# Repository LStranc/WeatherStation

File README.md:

# WeatherStation
The goal of this project was to build a cordless personal weather station that can be put in your own backyard. The weather station sends data to a server and you can analyze, store and use the data in anyway you want. 

This project includes c file to upload to the microcontroller, the server files used to store data in the sql database and display it to the website, and the schematic and pcb files for the actual hardware.

## Hardware
The Mircocontoller I used in this project is the esp32. A more generalized arudino code file is uploaded to this repo also. The weather station reads temperature, humidity, and pressure through a BME280 chip. It has a water sensor to sense if it is rainig. It uses the solar panel to tell how bright/sunny it is outside. This solar panel is also charging the lipo battery that it is powering the weather station. There is a uv sensor that tells us the uv index. There is Wind Sensor Rev P made by Modern Devices that is able to measure the windspeed. Also, there is a PWM5005 sensor which measures the air quality. The esp samples each sensor input then sends the data wirelessly to the server.

## Server
The server stores the data from the weather station and puts it in a mySQL database. The server also hosts a website where a client can interact with current and previously stored data. 

## Future 
This project is still in progress but the hope for the future is to implement an machine algorithm to try to forcast the upcoming weather.

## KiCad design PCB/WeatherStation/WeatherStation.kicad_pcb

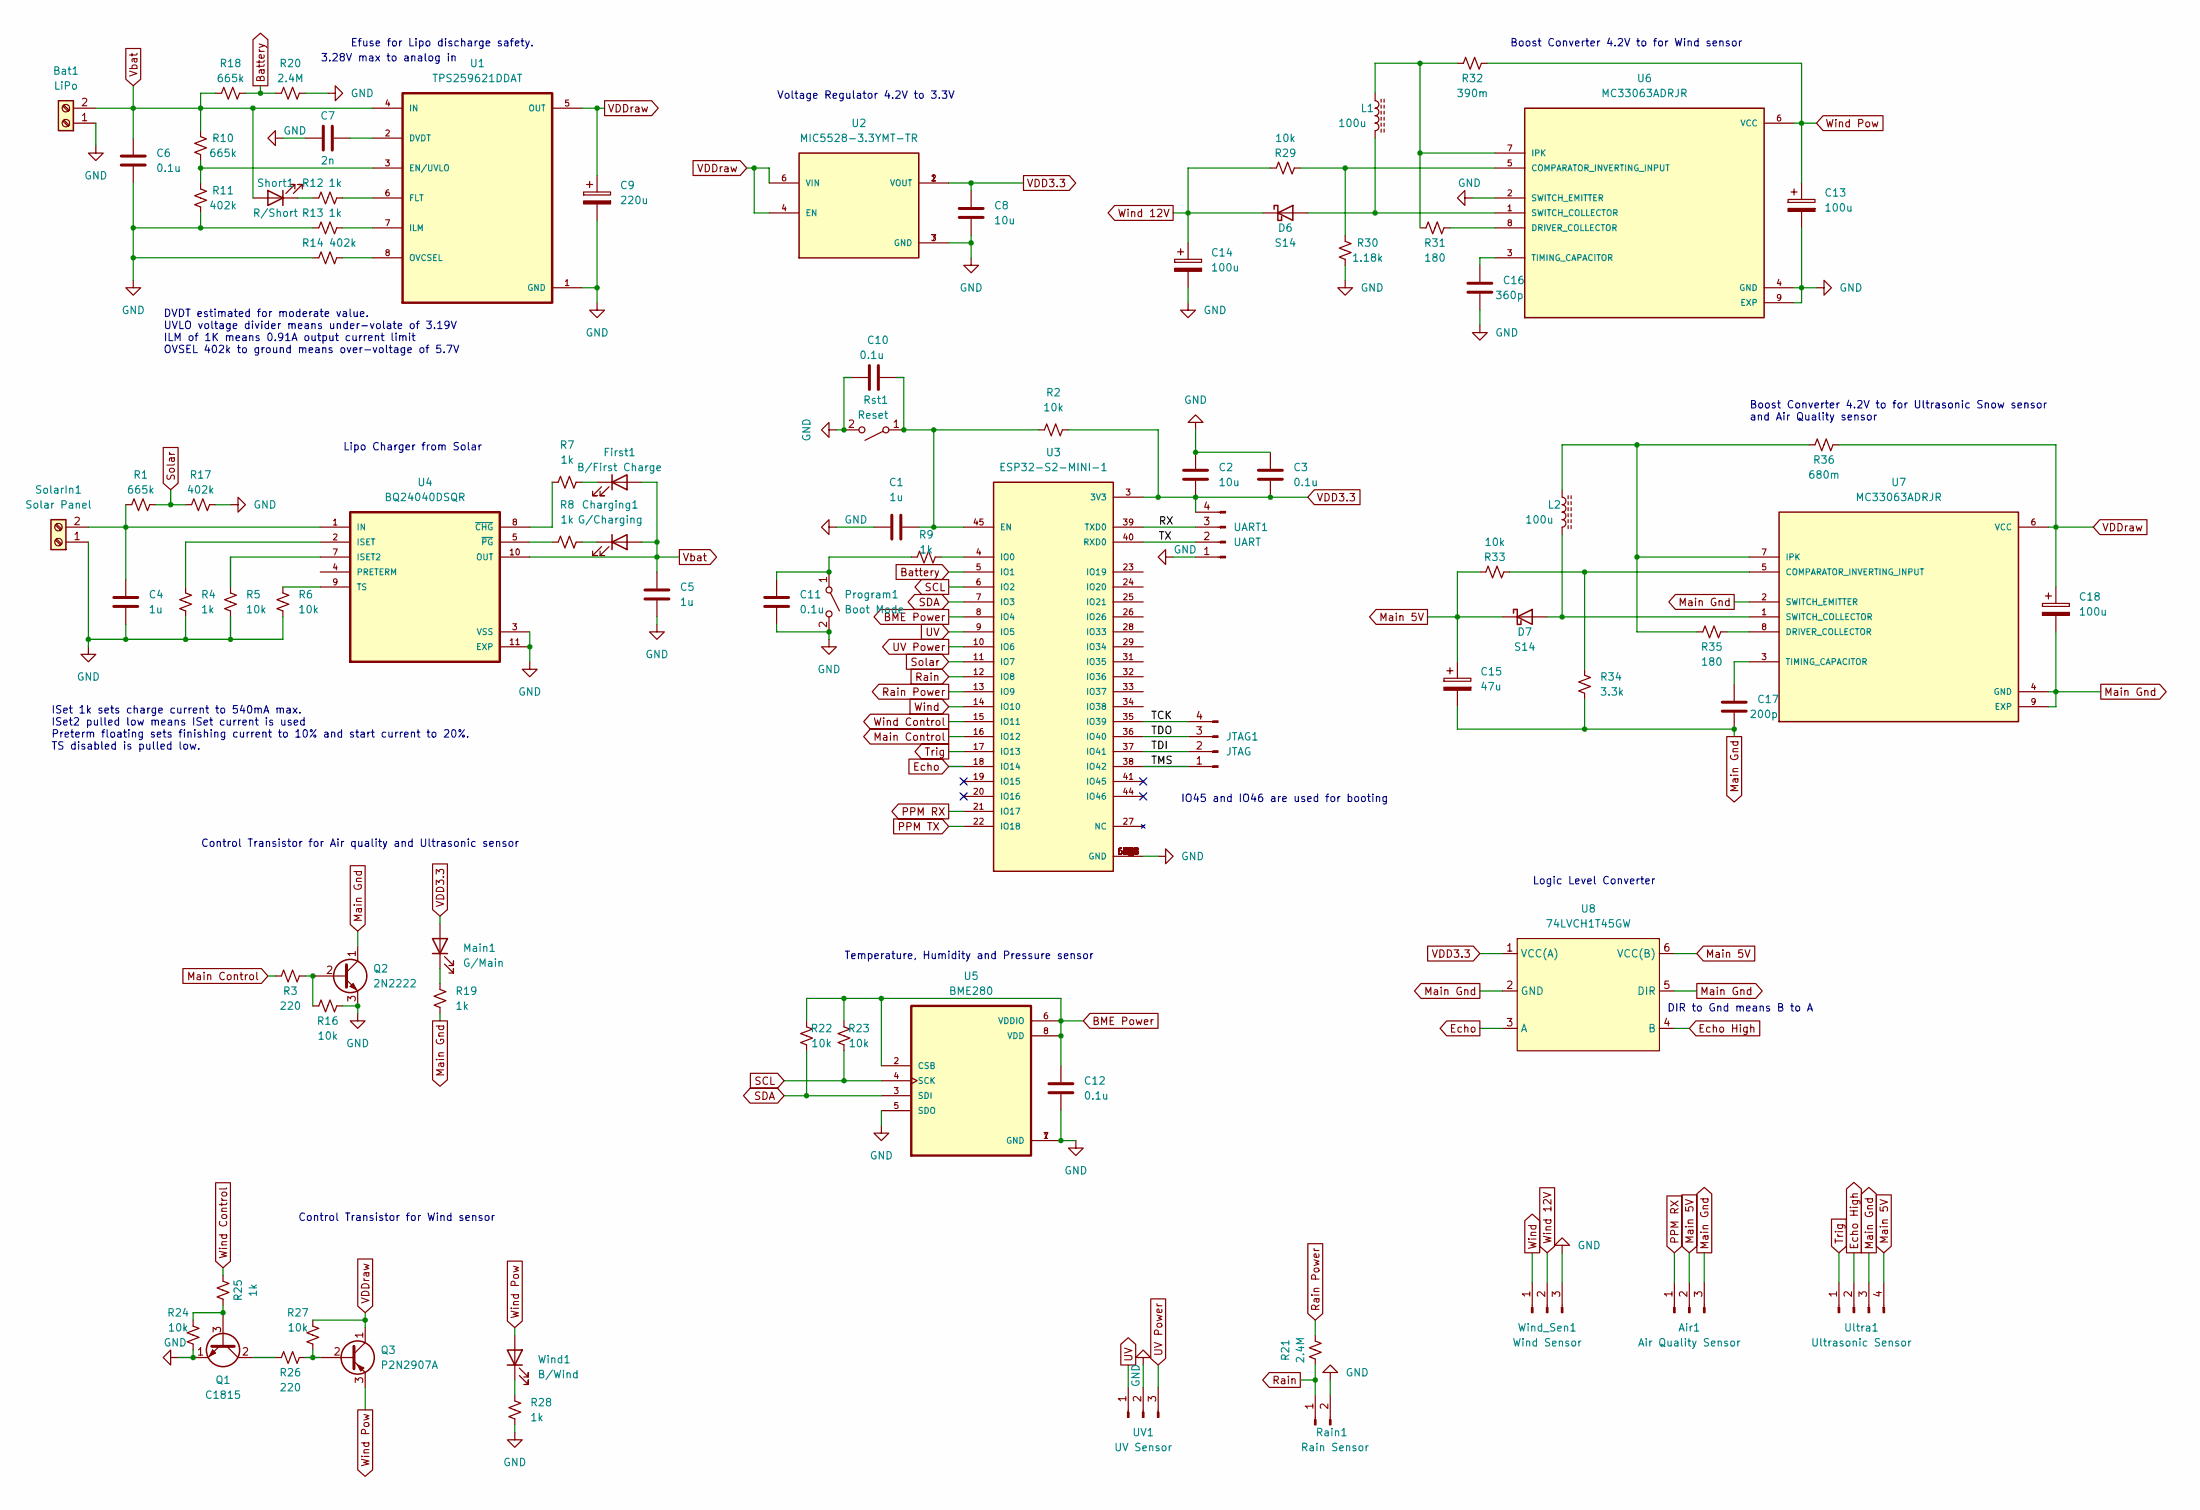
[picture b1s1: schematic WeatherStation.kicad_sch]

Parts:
Air1: Air Quality Sensor; PinHeader_1x03_P2.54mm_Vertical
Bat1: LiPo; TerminalBlock_Altech_AK300-2_P5.00mm
C1, C4, C5: 1u; C_0603_1608Metric_Pad1.08x0.95mm_HandSolder
C2, C8: 10u; C_0805_2012Metric_Pad1.18x1.45mm_HandSolder
C3, C6, C10, C11, C12: 0.1u; C_0603_1608Metric_Pad1.08x0.95mm_HandSolder
C7: 2n; C_0603_1608Metric_Pad1.08x0.95mm_HandSolder
C9: 220u; C_Radial_D5.0mm_H11.0mm_P2.00mm
C13, C18: 100u; C_Radial_D5.0mm_H11.0mm_P2.00mm
C14: 100u; C_Radial_D6.3mm_H11.0mm_P2.50mm
C15: 47u; C_Radial_D4.0mm_H7.0mm_P1.50mm
C16: 360p; C_0402_1005Metric_Pad0.74x0.62mm_HandSolder
C17: 200p; C_0603_1608Metric_Pad1.08x0.95mm_HandSolder
Charging1: G/Charging; LED_0603_1608Metric_Pad1.05x0.95mm_HandSolder
D6, D7: S14; D_SOD-123F
First1: B/First Charge; LED_0603_1608Metric_Pad1.05x0.95mm_HandSolder
JTAG1: JTAG; PinHeader_1x04_P2.54mm_Vertical
L1, L2: 100u; L_Toroid_Vertical_L10.2mm_W3.8mm_P3.8mm
Main1: G/Main; LED_0603_1608Metric_Pad1.05x0.95mm_HandSolder
Program1: Boot Mode; SW_PUSH_6mm_H5mm
Q1: C1815; TO-92
Q2: 2N2222; TO-92
Q3: P2N2907A; TO-92
R1, R10, R18: 665k; R_0603_1608Metric_Pad0.98x0.95mm_HandSolder
R2, R5, R6, R16, R22, R23, R24, R27, R29, R33: 10k; R_0603_1608Metric_Pad0.98x0.95mm_HandSolder
R3, R26: 220; R_0603_1608Metric_Pad0.98x0.95mm_HandSolder
R4, R7, R8, R9, R12, R13, R19, R25, R28: 1k; R_0603_1608Metric_Pad0.98x0.95mm_HandSolder
R11, R14, R17: 402k; R_0603_1608Metric_Pad0.98x0.95mm_HandSolder
R20, R21: 2.4M; R_0603_1608Metric_Pad0.98x0.95mm_HandSolder
R30: 1.18k; R_0603_1608Metric_Pad0.98x0.95mm_HandSolder
R31, R35: 180; R_0603_1608Metric_Pad0.98x0.95mm_HandSolder
R32: 390m; R_1206_3216Metric_Pad1.30x1.75mm_HandSolder
R34: 3.3k; R_0603_1608Metric_Pad0.98x0.95mm_HandSolder
R36: 680m; R_0603_1608Metric_Pad0.98x0.95mm_HandSolder
Rain1: Rain Sensor; PinHeader_1x02_P2.54mm_Vertical
Rst1: Reset; SW_PUSH_6mm_H5mm
Short1: R/Short; LED_0603_1608Metric_Pad1.05x0.95mm_HandSolder
SolarIn1: Solar Panel; TerminalBlock_Altech_AK300-2_P5.00mm
U1: TPS259621DDAT; VREG_LM5017MR_NOPB
U2: MIC5528-3.3YMT-TR; SON40P120X120X60-7N
U3: ESP32-S2-MINI-1; XCVR_ESP32-S2-MINI-1; PARTREV 1.0
U4: BQ24040DSQR; SON40P200X200X80-11N
U5: BME280; PSON65P250X250X100-8N
U6, U7: MC33063ADRJR; SON80P400X400X80-9N; PARTREV N
U8: 74LVCH1T45GW; SOT-363_SC-70-6_Handsoldering
UART1: UART; PinHeader_1x04_P2.54mm_Vertical
UV1: UV Sensor; PinHeader_1x03_P2.54mm_Vertical
Ultra1: Ultrasonic Sensor; PinHeader_1x04_P2.54mm_Vertical
Wind1: B/Wind; LED_0603_1608Metric_Pad1.05x0.95mm_HandSolder
Wind_Sen1: Wind Sensor; PinHeader_1x03_P2.54mm_Vertical

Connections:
/RX: U3.39 (TXD0), UART1.3
/TCK: JTAG1.4, U3.35 (IO39)
/TDI: JTAG1.2, U3.37 (IO41)
/TDO: JTAG1.3, U3.36 (IO40)
/TMS: JTAG1.1, U3.38 (IO42)
/TX: U3.40 (RXD0), UART1.2
BME Power: C12.1, R22.1, R23.1, U3.8 (IO4), U5.2 (CSB), U5.6 (VDDIO), U5.8 (VDD)
Battery: R18.2, R20.1, U3.5 (IO1)
Echo: U3.18 (IO14), U8.3 (A)
Echo High: U8.4 (B), Ultra1.2
GND: Bat1.1, C1.1, C2.1, C3.1, C4.1, C5.1, C6.2, C7.1, C8.2, C9.2, C10.2, C11.2, C12.2, C13.2, C14.2, C16.2, Program1.2 (B), Q1.1 (E), Q2.3 (E), R4.1, R5.1, R6.1, R11.2, R13.2, R14.2, R16.1, R17.2, R20.2, R24.2, R28.2, R30.1, Rain1.2, Rst1.2 (B), SolarIn1.1, U1.1 (GND), U2.3 (GND), U2.7 (GND), U3.1 (GND), U3.2 (GND), U3.30 (GND), U3.42 (GND), U3.43 (GND), U3.46 (GND), U3.47 (GND), U3.48 (GND), U3.49 (GND), U3.50 (GND), U3.51 (GND), U3.52 (GND), U3.53 (GND), U3.54 (GND), U3.55 (GND), U3.56 (GND), U3.57 (GND), U3.58 (GND), U3.59 (GND), U3.60 (GND), U3.61 (GND), U3.61_1 (GND), U3.61_2 (GND), U3.61_3 (GND), U3.61_4 (GND), U3.61_5 (GND), U3.61_6 (GND), U3.61_7 (GND), U3.61_8 (GND), U3.62 (GND), U3.63 (GND), U3.64 (GND), U3.65 (GND), U4.3 (VSS), U4.11 (EXP), U5.1 (GND), U5.5 (SDO), U5.7 (GND), U6.2 (SWITCH_EMITTER), U6.4 (GND), U6.9 (EXP), UART1.1, UV1.2, Wind_Sen1.3
Main 5V: Air1.2, C15.1, D7.1 (K), R33.2, U8.6 (VCC(B)), Ultra1.4
Main Control: R3.2, U3.16 (IO12)
Main Gnd: Air1.3, C15.2, C17.2, C18.2, Q2.1 (C), R19.2, R34.2, U7.2 (SWITCH_EMITTER), U7.4 (GND), U7.9 (EXP), U8.2 (GND), U8.5 (DIR), Ultra1.3
unnamed: C1.2, C10.1, R2.1, Rst1.1 (A), U3.45 (EN)
unnamed: C4.2, R1.1, SolarIn1.2, U4.1 (IN)
unnamed: C7.2, U1.2 (DVDT)
unnamed: C11.1, Program1.1 (A), R9.1
unnamed: C16.1, U6.3 (TIMING_CAPACITOR)
unnamed: C17.1, U7.3 (TIMING_CAPACITOR)
unnamed: Charging1.1 (K), R8.1
unnamed: D6.2 (A), L1.2, U6.1 (SWITCH_COLLECTOR)
unnamed: D7.2 (A), L2.2, U7.1 (SWITCH_COLLECTOR)
unnamed: First1.1 (K), R7.1
unnamed: L1.1, R31.1, R32.1, U6.7 (IPK)
unnamed: L2.1, R35.1, R36.1, U7.7 (IPK)
unnamed: Main1.1 (K), R19.1
unnamed: Q1.2 (C), R26.1
unnamed: Q1.3 (B), R24.1, R25.2
unnamed: Q2.2 (B), R3.1, R16.2
unnamed: Q3.2 (B), R26.2, R27.2
unnamed: R4.2, U4.2 (ISET)
unnamed: R5.2, U4.7 (ISET2)
unnamed: R6.2, U4.9 (TS)
unnamed: R7.2, U4.8 (~CHG)
unnamed: R8.2, U4.5 (~PG)
unnamed: R9.2, U3.4 (IO0)
unnamed: R10.2, R11.1, U1.3 (EN/UVLO)
unnamed: R12.1, U1.6 (FLT)
unnamed: R12.2, Short1.1 (K)
unnamed: R13.1, U1.7 (ILM)
unnamed: R14.1, U1.8 (OVCSEL)
unnamed: R28.1, Wind1.1 (K)
unnamed: R29.1, R30.2, U6.5 (COMPARATOR_INVERTING_INPUT)
unnamed: R31.2, U6.8 (DRIVER_COLLECTOR)
unnamed: R33.1, R34.1, U7.5 (COMPARATOR_INVERTING_INPUT)
unnamed: R35.2, U7.8 (DRIVER_COLLECTOR)
PPM RX: Air1.1, U3.21 (IO17)
PPM TX: U3.22 (IO18)
Rain: R21.1, Rain1.1, U3.12 (IO8)
Rain Power: R21.2, U3.13 (IO9)
SCL: R23.2, U3.6 (IO2), U5.4 (SCK)
SDA: R22.2, U3.7 (IO3), U5.3 (SDI)
Solar: R1.2, R17.1, U3.11 (IO7)
Trig: U3.17 (IO13), Ultra1.1
UV: U3.9 (IO5), UV1.1
UV Power: U3.10 (IO6), UV1.3
VDD3.3: C2.2, C3.2, C8.1, Main1.2 (A), R2.2, U2.1 (VOUT), U2.2 (VOUT), U3.3 (3V3), U8.1 (VCC(A)), UART1.4
VDDraw: C9.1, C18.1, Q3.1 (C), R27.1, R36.2, U1.5 (OUT), U2.4 (EN), U2.6 (VIN), U7.6 (VCC)
Vbat: Bat1.2, C5.2, C6.1, Charging1.2 (A), First1.2 (A), R10.1, R18.1, Short1.2 (A), U1.4 (IN), U4.10 (OUT)
Wind: U3.14 (IO10), Wind_Sen1.1
Wind 12V: C14.1, D6.1 (K), R29.2, Wind_Sen1.2
Wind Control: R25.1, U3.15 (IO11)
Wind Pow: C13.1, Q3.3 (E), R32.2, U6.6 (VCC), Wind1.2 (A)

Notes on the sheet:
Temperature, Humidity and Pressure sensor
3.28V max to analog in
DVDT estimated for moderate value. UVLO voltage divider means under-volate of 3.19V ILM of 1K means 0.91A output current limit OVSEL 402k to ground means over-voltage of 5.7V
IO45 and IO46 are used for booting
Logic Level Converter
DIR to Gnd means B to A
Lipo Charger from Solar
Boost Converter 4.2V to for Wind sensor
ISet 1k sets charge current to 540mA max. ISet2 pulled low means ISet current is used Preterm floating sets finishing current to 10% and start current to 20%. TS disabled is pulled low.
Control Transistor for Air quality and Ultrasonic sensor
Voltage Regulator 4.2V to 3.3V
Efuse for Lipo discharge safety.
Control Transistor for Wind sensor
Boost Converter 4.2V to for Ultrasonic Snow sensor and Air Quality sensor

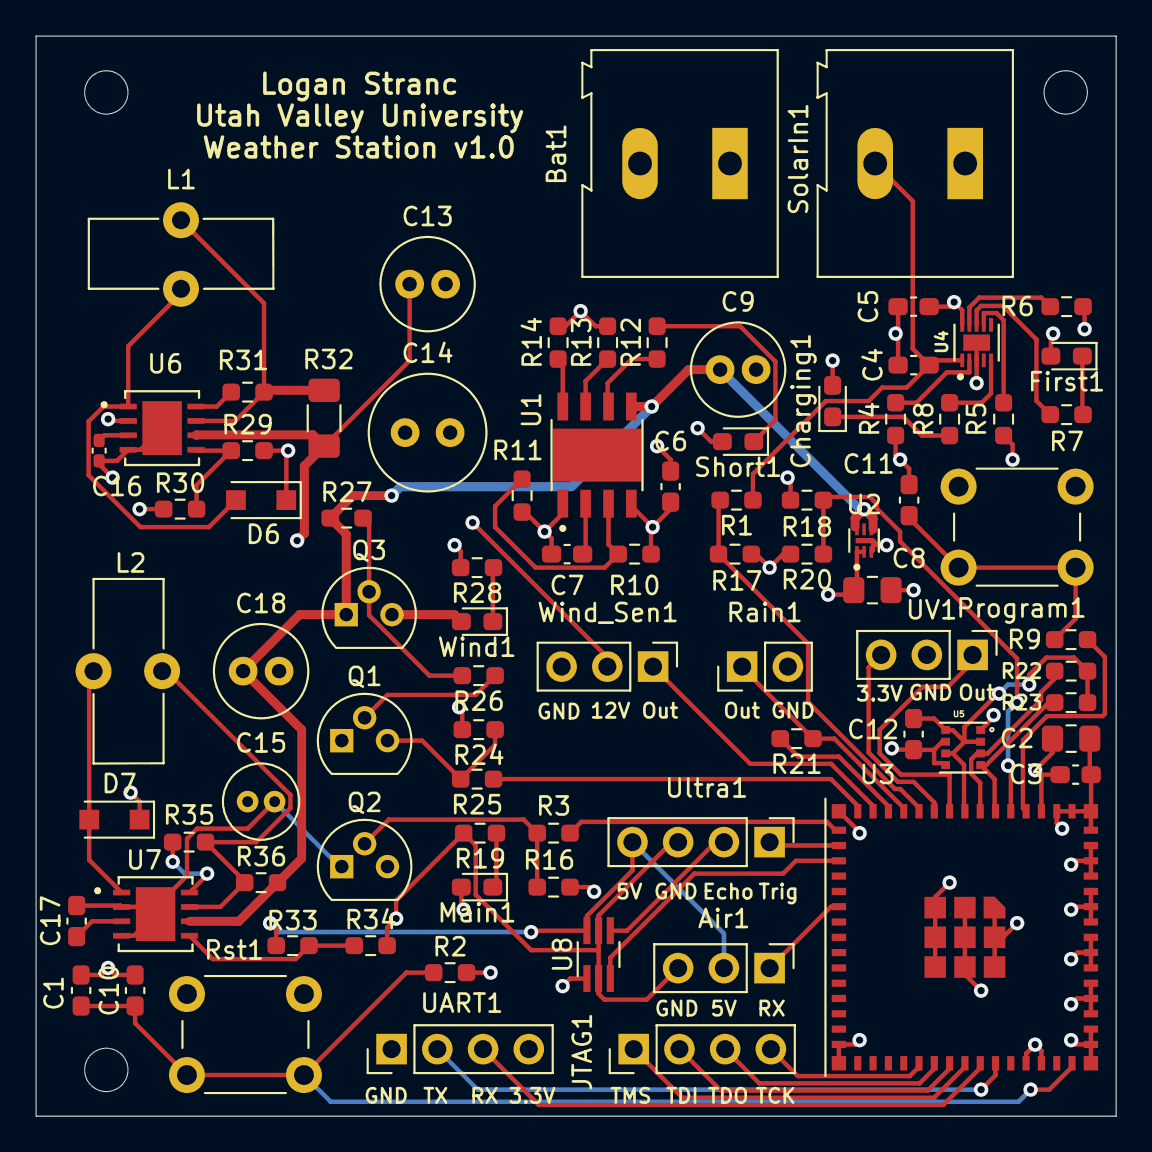
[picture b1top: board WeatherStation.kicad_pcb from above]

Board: 4 copper layers, 60.0 x 60.0 mm, 84 parts (0 on the bottom side), 63 nets.

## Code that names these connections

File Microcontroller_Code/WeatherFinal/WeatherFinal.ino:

#include "LowPower.h" //for sleep periods of microcontroller
#include <SoftwareSerial.h> // for serial communication needed for esp and air sensor
#include "Adafruit_PM25AQI.h" //air sensor library for easy interface
//BMP280 Packages
#include <Wire.h>
#include <Adafruit_Sensor.h>
#include <Adafruit_BME280.h>

#include "encrypt.h" //import ip and wifi connection information

// pins tx(pin 0) and rx(pin 1) are left floating
#define TRIGPIN 4 //ultrasonic trigger
#define ECHOPIN 5 //ultrasonic echo
#define POWERESP 8 //power for esp
#define POWERMAIN 9 //power for bme, rain, and uv sensors
#define POWERWIND 10 //power for wind sensor
#define BATTERYPIN A1 //battery voltage pin
#define SUNPIN A2 // solar panel voltage pin
#define WINDPIN A3 //wind sensor pin
#define UVPIN A6  // uv light sensor pin
#define RAINPIN A7 //Rain sensor pin

#define SERIALSPEED 115200               
#define DEBUG false 
SoftwareSerial esp8266(11,12);                   

SoftwareSerial pmSerial(2, 3); //only tx pin 2 is used, rx pin 3 is floating
Adafruit_PM25AQI aqi = Adafruit_PM25AQI();
PM25_AQI_Data data;

Adafruit_BME280 bme; // creates I2C BMP280 object, uses pins

float temperature = 0.0;
long pressure = 0;
float humidity = 0;
int precipitation = 0;
int sun = 800;
float windSpeed = 0;
int uvIndex = 1;
long cm = 0;
int battery = 0;

 
void setup(){
  Serial.begin(SERIALSPEED); 
  intPins();
}

void loop(){
  //sun = analogRead(SUNPIN); //store sun voltage reading
  deepSleep(30);
  battery = analogRead(BATTERYPIN); //store battery voltage reading
  delay(5000);
  readMainBus(); //reads data from bme, rain, and uv sensor
  delay(5000); // heavy load to heavy load, let circuit reach steady state 
  readWindBus(); // reads data from wind sensor
  delay(5000);
  sendWiFiOnBus(); //powerup and initialize esp and send weather data
  deepSleep(5); // sleep for 5*8= 40seconds
}

void deepSleep(int EightSecondIntervals){
  int i = 0;
  while(i<EightSecondIntervals){
  LowPower.powerDown(SLEEP_8S, ADC_OFF, BOD_OFF); //deep sleep for 8 seconds
  i++;
  } 
}

void intPins(){
  pinMode(POWERMAIN,OUTPUT);
  pinMode(POWERWIND,OUTPUT);
  pinMode(POWERESP,OUTPUT);
  digitalWrite(POWERMAIN, LOW);
  digitalWrite(POWERWIND, LOW);
  digitalWrite(POWERESP, LOW);

  
  //Ultrasonic sensor setup pins
  pinMode(TRIGPIN, INPUT); //InputPullup = 28uA, Input = 0 uA
  pinMode(ECHOPIN, INPUT); //InputPullup = 33 uA, Input
}

void readMainBus(){
  digitalWrite(POWERMAIN,HIGH); //give main bus power
  pinMode(TRIGPIN,OUTPUT);
  pinMode(ECHOPIN, INPUT); // set echo pin back to input
  delay(500);
  bme.begin(0x76); // bme initialize
  delay(2000); 
  temperature = bme.readTemperature(); //store temperature
  pressure = bme.readPressure(); //store pressure
  humidity = bme.readHumidity(); //store humidity
  delay(500);
  uvIndex = analogRead(UVPIN); //store uv voltage reading
  precipitation = analogRead(RAINPIN); //store precipitation voltage reading
  delay(1000);
  snowSensorRead(); // read snow height data
  delay(15000); //let sensor warmup for 15 seconds  
  airSensorRead(); // read air quality data 
  pinMode(TRIGPIN, INPUT); //set trigpin back to input pullup to convserve power
  digitalWrite(POWERMAIN,LOW);
}

void airSensorRead(){
  pmSerial.begin(9600); //begin serial communication with air sensor
  while (! aqi.begin_UART(&pmSerial)){ // wait while air sensor has not begun serial communication
    digitalWrite(13, HIGH);
    delay(1000);
    digitalWrite(13,LOW);
    delay(1000);
  }
  while (! aqi.read(&data) && data.particles_03um <= 1) { //wait until good data is read, values are stored in data struct
    digitalWrite(13, HIGH);
    delay(250);
    digitalWrite(13,LOW);
    delay(250);
  }  
}

void snowSensorRead(){
  long duration;
  //Ultrasonic Snow Sensor Reading
  // The sensor is triggered by a HIGH pulse of 10 or more microseconds.
  // Give a short LOW pulse beforehand to ensure a clean HIGH pulse:.
  digitalWrite(TRIGPIN, LOW);
  delayMicroseconds(5);
  digitalWrite(TRIGPIN, HIGH);
  delayMicroseconds(10);
  digitalWrite(TRIGPIN, LOW);
  // Read the signal from the sensor: a HIGH pulse whose
  // duration is the time (in microseconds) from the sending
  // of the ping to the reception of its echo off of an object.
  duration = pulseIn(ECHOPIN, HIGH);
  // Convert the time into a distance
  cm = (duration/2) / 29.1;     // Divide by 29.1 or multiply by 0.0343
  //Assuming the sensor is 86 cm from the ground the difference between the distance
  // the ultrasonic sensor found and the actual ground will be the amount of snowfall
  // this calculation is done server side
}

void readWindBus(){
  digitalWrite(POWERWIND,HIGH); // give power to 3.3 to 12V step for wind sensor
  delay(30000); // wait a while for the sensor to heat up
  windSpeed = analogRead(WINDPIN);
  windSpeed =  pow(((((float)windSpeed) - 264.0) / 85.6814), 3.36814); //equation converts voltage read at output into wind speed in mph
  digitalWrite(POWERWIND,LOW); // turn off wind bus
}

String sendData(String command, const int timeout, boolean debug)
{
    String response = "";                                             
    esp8266.print(command);                                          
    long int time = millis();                                      
    while( (time+timeout) > millis())                                 
    {      
      while(esp8266.available())                                      
      {
        char c = esp8266.read();                                     
        response+=c;                                                  
      }  
    }    
    if(debug)                                                        
    {
      //Serial.print(response);
    }    
    return response;                                                  
}

void initWifiModule()
{
  String wifi_username = get_WiFi_Username();
  String wifi_password = get_WiFi_Password();
  
  esp8266.begin(SERIALSPEED);
  delay(1000);
  sendData("AT+RST\r\n", 2000, DEBUG); 
  sendData("AT+CWJAP=\"" + wifi_username + "\",\"" + wifi_password + "\"\r\n", 2000, DEBUG);        
  delay (3000);
  sendData("AT+CWMODE=1\r\n", 2000, DEBUG);                                          
  delay (1500);
  sendData("AT+CIFSR\r\n", 2000, DEBUG);                                                                    
  delay (1500);
  sendData("AT+CIPMUX=1\r\n", 2000, DEBUG);                                                                            
}

void sendWeatherData(){
  String ip = get_IP();
  
  sendData("AT+CIPSTART=0,\"TCP\",\"" + ip + "\",80\r\n", 6000, DEBUG); //attempt to start tcp communication with server port 80                              
  delay(500);
  String message = String("GET ") + "/receiverDB.php?" + 
              "temp="+ temperature +
              "&humidity=" + humidity +
              "&pressure=" + pressure +
              "&precipitation=" + precipitation +
              "&windspeed=" + windSpeed +
              "&sun=" + sun +
              "&parta=" + data.particles_03um +
              "&partb=" + data.particles_05um +
              "&partc=" + data.particles_10um +
              "&partd=" + data.particles_25um +
              "&parte=" + data.particles_50um +
              "&partf=" + data.particles_100um +
              "&uvindex=" + uvIndex +
              "&snowfall=" + cm +
              "&battery=" + battery + 
              " HTTP/1.1\r\n" + 
              "Host: " + ip + "\r\n\r\n"; //GET request of all data to be sent to server_ip/receiverDB.php     
   String cipSend = "AT+CIPSEND=0,";
   cipSend +=message.length(); 
   cipSend +="\r\n";
   delay(2000);
   sendData(cipSend,4000,DEBUG); //send full GET request message
   delay(2000);
   sendData(message,4000,DEBUG); //resend message
   String closeCommand = "AT+CIPCLOSE=0"; 
   closeCommand+="\r\n";  
   delay(2000);  
   sendData(closeCommand,4000,DEBUG); //close connection with server
}

void sendWiFiOnBus(){
  digitalWrite(POWERESP, HIGH);
  delay(500);
  initWifiModule(); //initialize esp on network settings
  delay(2000);
  sendWeatherData();
  delay(1000);
  digitalWrite(POWERESP,LOW);
}

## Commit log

2023-04-28 Added Git Ignore
2023-04-28 Rough draft of Control PCB with Gerbers
2023-12-11 PCB Gerber Files
